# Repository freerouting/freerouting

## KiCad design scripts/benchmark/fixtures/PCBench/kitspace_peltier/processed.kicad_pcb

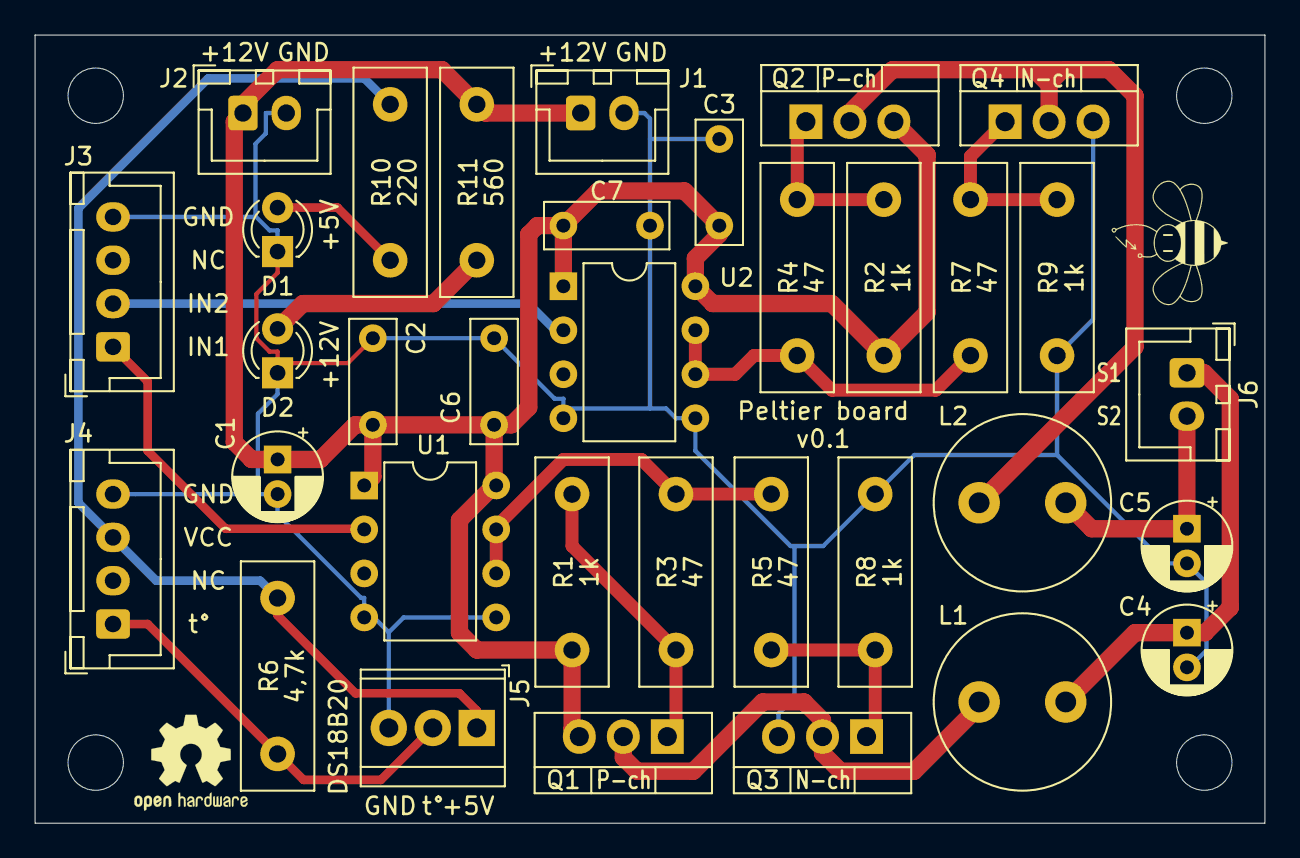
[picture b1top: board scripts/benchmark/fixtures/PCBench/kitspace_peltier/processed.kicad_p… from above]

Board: 2 copper layers, 71.0 x 45.5 mm, 34 parts (0 on the bottom side), 18 nets.

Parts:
C1, C4, C5: 22u; CP_Radial_D5.0mm_P2.00mm
C2, C3, C6, C7: 100nF; C_Disc_D7.0mm_W2.5mm_P5.00mm
D1, D2: LED; LED_D3.0mm
J1, J2, J6: Conn_01x02; JST_XH_B2B-XH-A_1x02_P2.50mm_Vertical
J3, J4: Conn_01x04; JST_XH_B4B-XH-A_1x04_P2.50mm_Vertical
J5: Conn_01x03; TerminalBlock_TE_282834-3_1x03_P2.54mm_Horizontal
L1, L2: 33u; L_Radial_D10.0mm_P5.00mm_Neosid_SD12_style3
Q1, Q2: IRF9Z34NPBF; TO-220-3_Vertical
Q3, Q4: IRFZ24NPBF; TO-220-3_Vertical
R1, R2, R8, R9: 1k; R_Box_L13.0mm_W4.0mm_P9.00mm
R3, R4, R5, R7: 47; R_Box_L13.0mm_W4.0mm_P9.00mm
R6: 4,7k; R_Box_L13.0mm_W4.0mm_P9.00mm
R10: 220; R_Box_L13.0mm_W4.0mm_P9.00mm
R11: 560; R_Box_L13.0mm_W4.0mm_P9.00mm
U1, U2: TC4420CPA; DIP-8_W7.62mm

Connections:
+5V: J4.3, J5.1, R6.2, R10.1
+12V: C1.1, C2.1, C3.1, C6.1, C7.1, J1.1, J2.1, Q1.3, Q2.3, R1.2, R2.2, R11.1, U1.1, U1.8, U2.1, U2.8
GND: C1.2, C2.2, C3.2, C4.2, C5.2, C6.2, C7.2, D1.1, D2.1, J1.2, J2.2, J3.4, J4.4, J5.3, Q3.3, Q4.3, R8.1, R9.1, U1.4, U1.5, U2.4, U2.5
IN1: J3.1, U1.2
IN2: J3.2, U2.2
unnamed: C4.1, J6.1, L1.2
unnamed: C5.1, J6.2, L2.2
unnamed: D1.2, R10.2
unnamed: D2.2, R11.2
unnamed: L1.1, Q1.2, Q3.2
unnamed: L2.1, Q2.2, Q4.2
unnamed: Q1.1, R1.1, R3.2
unnamed: Q2.1, R2.1, R4.2
unnamed: Q3.1, R5.2, R8.2
unnamed: Q4.1, R7.2, R9.2
unnamed: R3.1, R5.1, U1.6, U1.7
unnamed: R4.1, R7.1, U2.6, U2.7
t: J4.1, J5.2, R6.1

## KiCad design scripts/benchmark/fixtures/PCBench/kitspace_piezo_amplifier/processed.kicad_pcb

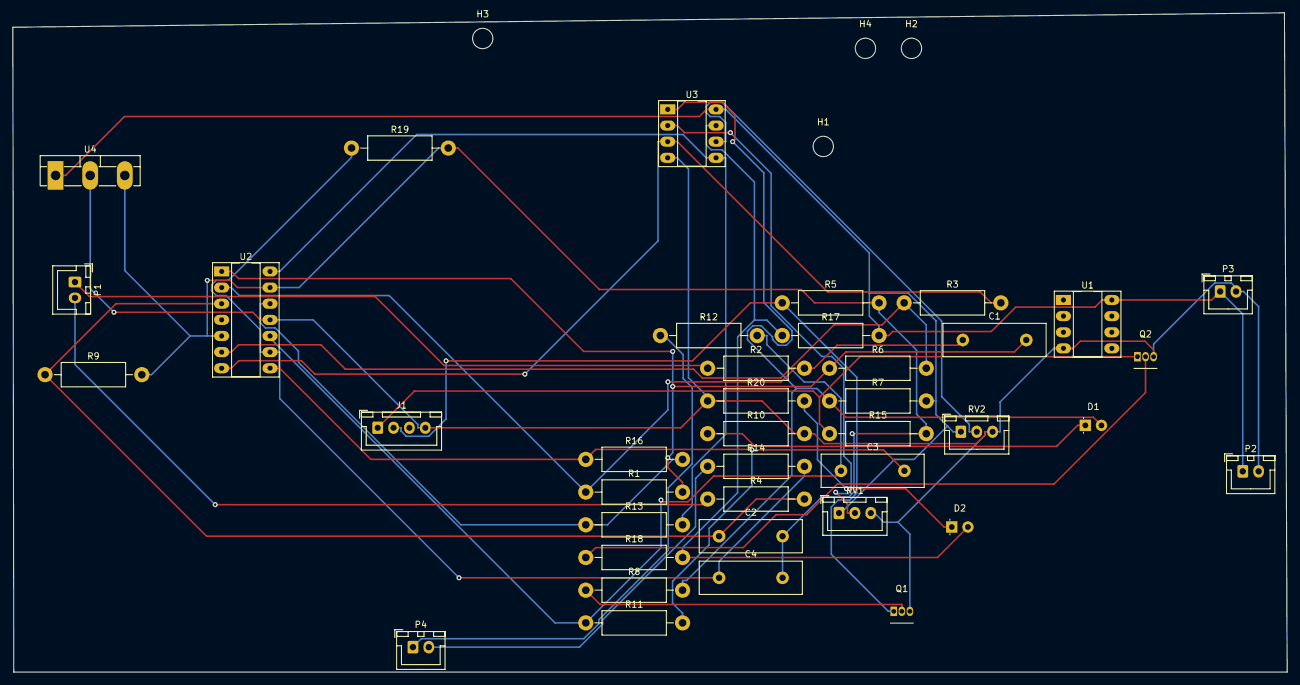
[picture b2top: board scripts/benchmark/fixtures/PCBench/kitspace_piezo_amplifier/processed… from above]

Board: 2 copper layers, 200.7 x 103.8 mm, 43 parts (0 on the bottom side), 27 nets.

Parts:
C1, C2, C3, C4: 22pF; C_Disc_D16.0mm_W5.0mm_P10.00mm
D1, D2: LED; LED_D3.0mm_Clear
H1, H2, H3, H4: MountingHole; MountingHole_3.2mm_M3_ISO7380
J1: Conn_01x04_Female; JST_XH_B4B-XH-A_1x04_P2.50mm_Vertical
P1: piezzo1; JST_XH_B2B-XH-A_1x02_P2.50mm_Vertical
P2, P3: 12V; JST_XH_B2B-XH-A_1x02_P2.50mm_Vertical
P4: piezzo2; JST_XH_B2B-XH-A_1x02_P2.50mm_Vertical
Q1, Q2: PN2222A; TO-92_Inline
R1, R9, R11, R19: 100M; R_Axial_DIN0411_L9.9mm_D3.6mm_P15.24mm_Horizontal
R2, R4, R6, R12, R14, R16: 10k; R_Axial_DIN0411_L9.9mm_D3.6mm_P15.24mm_Horizontal
R3, R13: 20k; R_Axial_DIN0411_L9.9mm_D3.6mm_P15.24mm_Horizontal
R5, R7, R15, R17: 3k; R_Axial_DIN0411_L9.9mm_D3.6mm_P15.24mm_Horizontal
R8, R10, R18, R20: 270; R_Axial_DIN0411_L9.9mm_D3.6mm_P15.24mm_Horizontal
RV1, RV2: R_Potentiometer; JST_XH_B3B-XH-A_1x03_P2.50mm_Vertical
U1, U3: LM393; DIP-8_W7.62mm_Socket_LongPads
U2: Opamp_Quad; DIP-14_W7.62mm_Socket_LongPads
U4: L7806; TO-3P-3_Vertical

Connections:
+6V: C2.2, C4.2, R5.2, R9.2, R15.2, R19.2, U2.5, U2.13, U4.3
+12V: P2.1, P3.1, R7.2, R17.2, RV1.1, RV2.1, U1.8, U3.8, U4.1
GND: J1.4, P2.2, P3.2, Q1.3, Q2.3, R10.2, R20.1, RV1.3, RV2.3, U1.4, U2.11, U3.4, U4.2
unnamed: C1.1, R1.1, R2.2, U2.2
unnamed: C1.2, R1.2, R6.1, U2.1
unnamed: C2.1, R4.2, R9.1, U2.3
unnamed: C3.1, R11.1, R12.2, U2.10
unnamed: C3.2, R11.2, R16.1, U2.8
unnamed: C4.1, R14.2, R19.1, U2.9
unnamed: D1.1, R10.1
unnamed: D1.2, R7.1, R8.2, U3.1
unnamed: D2.1, R20.2
unnamed: D2.2, R17.1, R18.2, U3.7
unnamed: J1.1, Q2.1, R15.1
unnamed: J1.2, Q1.1, R5.1
unnamed: P1.1, R2.1
unnamed: P1.2, R4.1
unnamed: P4.1, R12.1
unnamed: P4.2, R14.1
unnamed: Q1.2, R8.1
unnamed: Q2.2, R18.1
unnamed: R3.1, R6.2, U2.6
unnamed: R3.2, U2.7, U3.3
unnamed: R13.1, R16.2, U2.12
unnamed: R13.2, U2.14, U3.5
unnamed: RV1.2, U3.2
unnamed: RV2.2, U3.6

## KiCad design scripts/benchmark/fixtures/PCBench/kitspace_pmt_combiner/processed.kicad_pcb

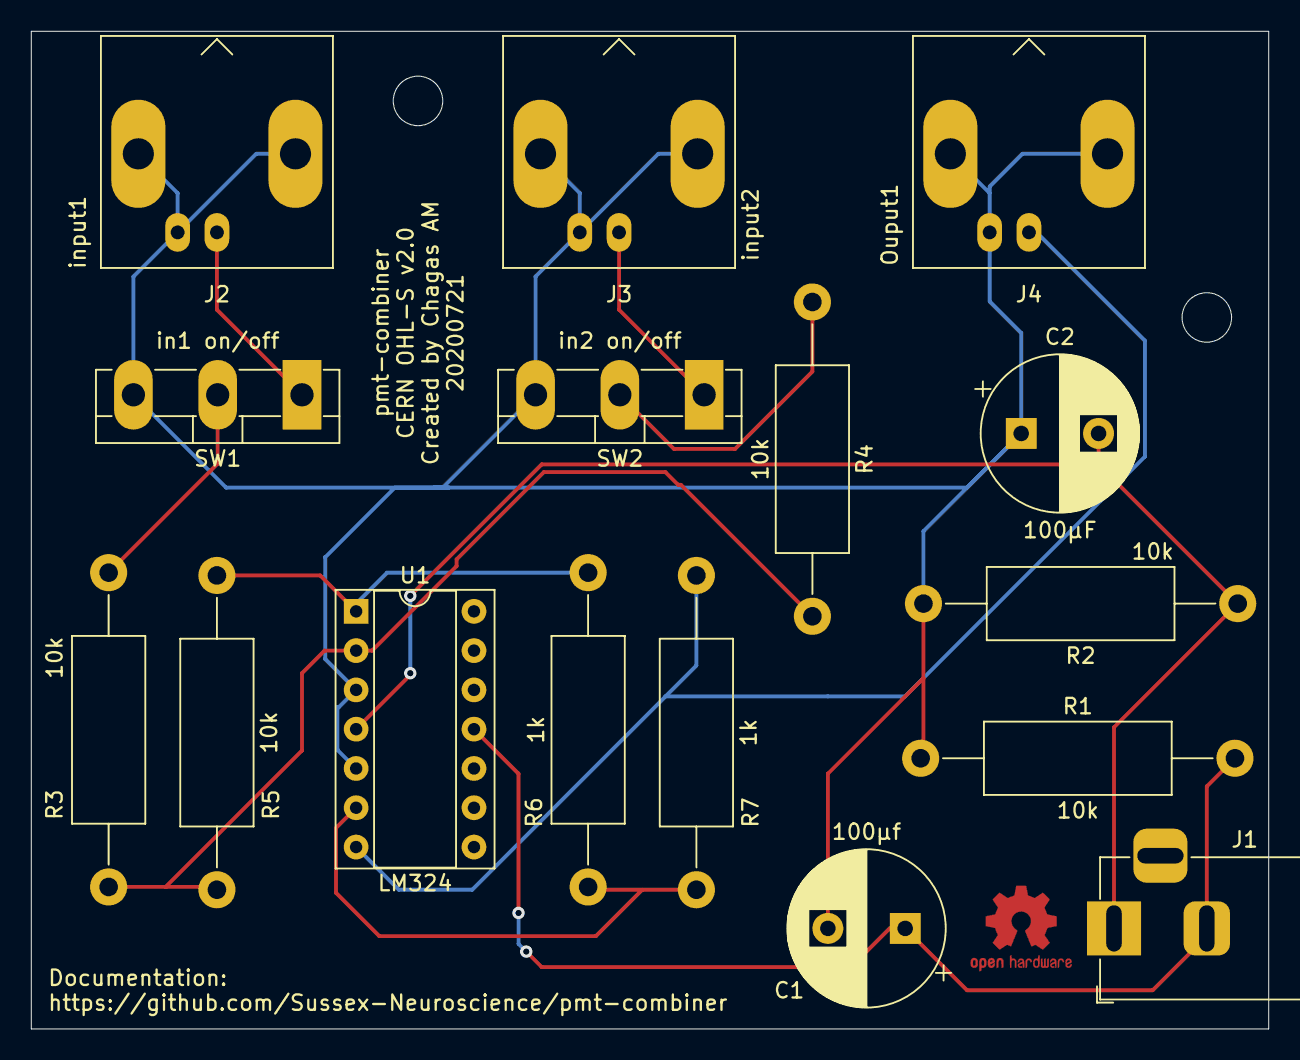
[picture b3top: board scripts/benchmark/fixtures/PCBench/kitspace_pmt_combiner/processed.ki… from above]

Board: 2 copper layers, 80.0 x 64.5 mm, 16 parts (0 on the bottom side), 11 nets.

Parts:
C1: 100µf; CP_Radial_D10.0mm_P5.00mm
C2: 100µF; CP_Radial_D10.0mm_P5.00mm
J1: Barrel_Jack_MountingPin; BarrelJack_Horizontal
J2: input1; BNC_Amphenol_B6252HB-NPP3G-50_Horizontal
J3: input2; BNC_Amphenol_B6252HB-NPP3G-50_Horizontal
J4: Ouput1; BNC_Amphenol_B6252HB-NPP3G-50_Horizontal
R1, R2, R3, R4, R5: 10k; R_Axial_DIN0414_L11.9mm_D4.5mm_P20.32mm_Horizontal
R6, R7: 1k; R_Axial_DIN0414_L11.9mm_D4.5mm_P20.32mm_Horizontal
SW1: in1 on/off; TO-3P-3_Vertical
SW2: in2 on/off; TO-3P-3_Vertical
U1: LM324; DIP-14_W7.62mm_Socket

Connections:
GND: C1.2, C2.1, J2.2, J3.2, J4.2, R1.1, R2.2, SW1.3, SW2.3, U1.3, U1.5
unnamed: C1.1, J1.2, R1.2, U1.11
unnamed: C2.2, J1.1, R2.1, U1.4
unnamed: J2.1, SW1.1
unnamed: J3.1, SW2.1
unnamed: J4.1, R7.2, U1.7
unnamed: R3.1, SW1.2
unnamed: R3.2, R4.2, R5.1, U1.2
unnamed: R4.1, SW2.2
unnamed: R5.2, R6.1, U1.1
unnamed: R6.2, R7.1, U1.6

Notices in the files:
scripts/benchmark/fixtures/PCBench/kitspace_pmt_combiner/processed.kicad_pcb:
CERN OHL-S v2.0
